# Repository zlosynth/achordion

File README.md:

# Achordion

Chord-crafting quantizing wavetable oscillator module for Eurorack.

* Wavetable synthesis, 37 wavetables, smooth transitions
* Up to 18 simultaneous voices
* Sub-octaves, duplicated tones, and chords
* 4 styles of playing - single tone, chords, arpeggios, intervals
* Quantization to selected scale
* Any scale can be played with the white piano keys
* Two lines with independent 1V/oct inputs and audio outputs
* LEDs visualizing dialed parameters
* Based around Electro-Smith's [Daisy Patch SM](https://www.electro-smith.com/daisy/patch-sm) platform
* Programmed in Rust

Find more details about the module, including a feature overview video and a
user manual, on its [website](https://zlosynth.com/achordion).

# Firmware

If you wish to upgrade to a newer version of firmware, refer to the respective
[Release description](https://github.com/zlosynth/achordion/releases).

# Development

See [DEVELOPMENT.md](DEVELOPMENT.md) to find some basic commands to interact
with the project. To learn more, read the code. A good place to start would be
[eurorack/src/main.rs](eurorack/src/main.rs).

# License

Software of Achordion is distributed under the terms of the General Public
License version 3. See [LICENSE-SOFTWARE](LICENSE-SOFTWARE) for details.

Schematics and PCB layout are distributed under the terms of Creative Commons
BY-SA. See [LICENSE-HARDWARE](LICENSE-HARDWARE) for details. Parts of the
schematics are based on [Emilie Gillet's Mutable
Instruments](https://github.com/pichenettes/eurorack), kudos to her for making
them open.

The manual is distributed under the terms of Creative Commons BY-SA too. See
[LICENSE-MANUAL](LICENSE-MANUAL) for details.

# Changelog

Read the [CHANGELOG.md](CHANGELOG.md) to learn about changes introduced in each
release.

# Versioning

See [VERSIONING.md](VERSIONING.md) to find detailed information about versioning
of the project and compatability between its software and hardware.

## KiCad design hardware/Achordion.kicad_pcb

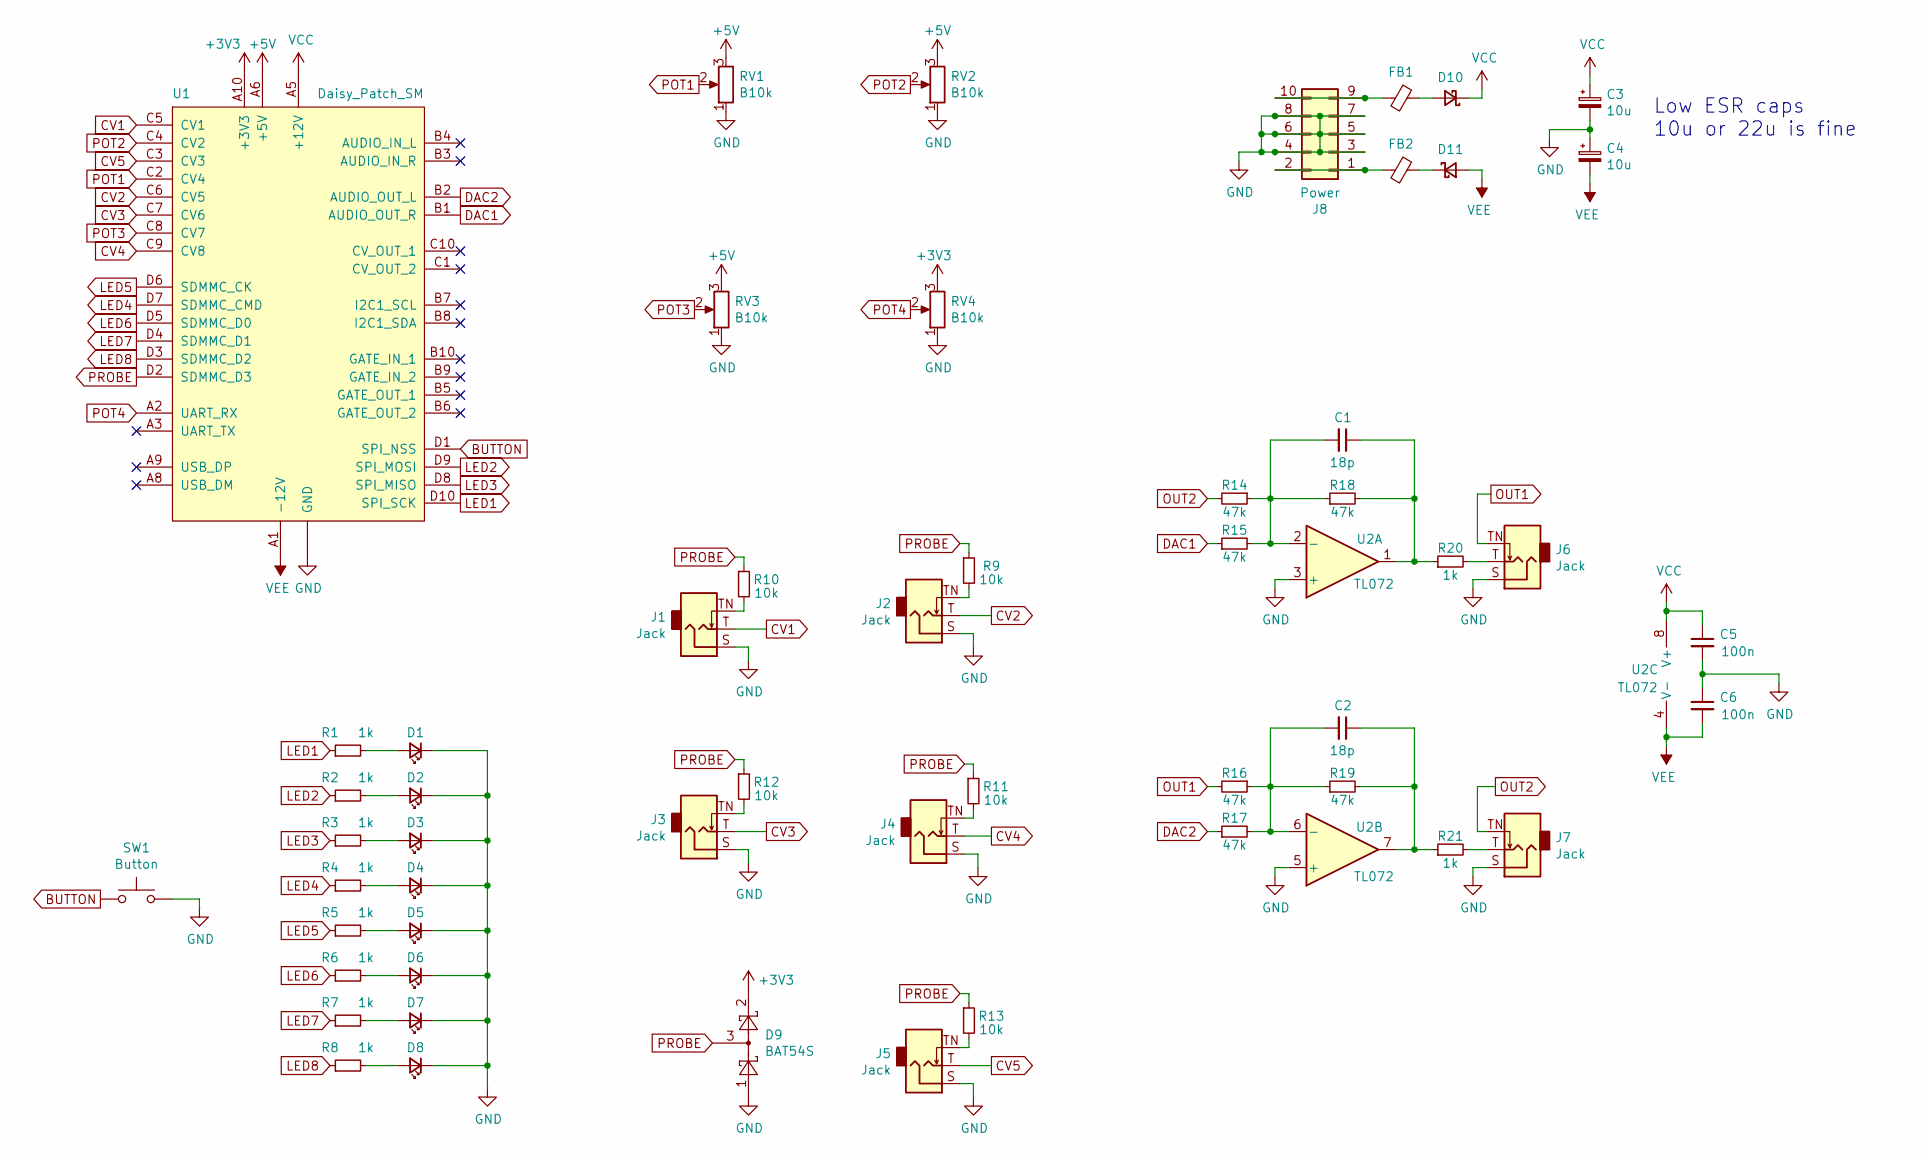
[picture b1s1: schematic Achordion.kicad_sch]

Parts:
C1, C2: 18p; C_0805_2012Metric_Pad1.18x1.45mm_HandSolder; Mfr Part Number CL10C180JB81PNC; LCSC C1647
C3, C4: 10u; CP_Elec_5x5.8; Mfr Part Number T491B226M016AT; LCSC C122226
C5, C6: 100n; C_0805_2012Metric_Pad1.18x1.45mm_HandSolder; Mfr Part Number CL10F104ZO8NNNC; LCSC C14663
D1, D2, D3, D4, D5, D6, D7, D8: LED; LED_D3.0mm; Mfr Part Number WP710A10SRD/D
D9: BAT54S; SOT-23_Handsoldering; Mfr Part Number BAT54S,215
D10, D11: Schottky; D_SOD-123; Mfr Part Number STPS0540ZY; LCSC C8598
FB1, FB2: FB; L_0805_2012Metric_Pad1.05x1.20mm_HandSolder
J1, J2, J3, J4, J5, J6, J7: Jack; Jack_3.5mm_QingPu_WQP-PJ398SM_Vertical_CircularHoles
J8: Power; Power_Connector_Connfly; Mfr Part Number 87914-1016
R1, R2, R3, R4, R5, R6, R7, R8: 1k; R_0805_2012Metric_Pad1.20x1.40mm_HandSolder; Mfr Part Number CR0603-FX-3650ELF; LCSC C23032
R9, R10, R11, R12, R13: 10k; R_0805_2012Metric_Pad1.20x1.40mm_HandSolder; Mfr Part Number CR0603-FX-1002ELF; LCSC C25744
R14, R16, R18, R19: 47k; R_0805_2012Metric_Pad1.20x1.40mm_HandSolder; Mfr Part Number CR0603-FX-4702ELF; LCSC C25819
R15, R17: 47k; R_0805_2012Metric_Pad1.20x1.40mm_HandSolder; Mfr Part Number CR0603-JW-682ELF; LCSC C23212
R20, R21: 1k; R_0805_2012Metric_Pad1.20x1.40mm_HandSolder; Mfr Part Number CR0603-FX-1001ELF; LCSC C21190
RV1, RV2, RV3, RV4: B10k; Potentiometer_Alpha; Mfr Part Number RK09L1140A66
SW1: Button; SW_PUSH_6mm; Mfr Part Number SKHHDTA010
U1: Daisy_Patch_SM
U2: TL072; SOIC-8_3.9x4.9mm_P1.27mm; Mfr Part Number TL072CD; LCSC C163525

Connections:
+3V3: D9.2, RV4.3, U1.A10 (+3V3)
+5V: RV1.3, RV2.3, RV3.3, U1.A6 (+5V)
BUTTON: SW1.1, U1.D1 (SPI_NSS)
CV1: J1.T, U1.C5 (CV1)
CV2: J2.T, U1.C6 (CV5)
CV3: J3.T, U1.C7 (CV6)
CV4: J4.T, U1.C9 (CV8)
CV5: J5.T, U1.C3 (CV3)
DAC1: R15.1, U1.B1 (AUDIO_OUT_R)
DAC2: R17.1, U1.B2 (AUDIO_OUT_L)
GND: C3.2, C4.1, C5.2, C6.1, D1.1 (K), D2.1 (K), D3.1 (K), D4.1 (K), D5.1 (K), D6.1 (K), D7.1 (K), D8.1 (K), D9.1, J1.S, J2.S, J3.S, J4.S, J5.S, J6.S, J7.S, J8.3, J8.4, J8.5, J8.6, J8.7, J8.8, RV1.1, RV2.1, RV3.1, RV4.1, SW1.2, U1.A4 (GND), U1.A7 (GND), U2.3 (+), U2.5 (+)
LED1: R1.1, U1.D10 (SPI_SCK)
LED2: R2.1, U1.D9 (SPI_MOSI)
LED3: R3.1, U1.D8 (SPI_MISO)
LED4: R4.1, U1.D7 (SDMMC_CMD)
LED5: R5.1, U1.D6 (SDMMC_CK)
LED6: R6.1, U1.D5 (SDMMC_D0)
LED7: R7.1, U1.D4 (SDMMC_D1)
LED8: R8.1, U1.D3 (SDMMC_D2)
unnamed: C1.1, R18.2, R20.1, U2.1
unnamed: C2.1, R19.2, R21.1, U2.7
unnamed: D1.2 (A), R1.2
unnamed: D2.2 (A), R2.2
unnamed: D3.2 (A), R3.2
unnamed: D4.2 (A), R4.2
unnamed: D5.2 (A), R5.2
unnamed: D6.2 (A), R6.2
unnamed: D7.2 (A), R7.2
unnamed: D8.2 (A), R8.2
unnamed: D10.2 (A), FB1.1
unnamed: D11.1 (K), FB2.1
unnamed: J1.TN, R10.2
unnamed: J2.TN, R9.2
unnamed: J3.TN, R12.2
unnamed: J4.TN, R11.2
unnamed: J5.TN, R13.2
unnamed: J6.T, R20.2
unnamed: J7.T, R21.2
unnamed: FB2.2, J8.1, J8.2
unnamed: FB1.2, J8.9, J8.10
unnamed: C1.2, R14.1, R15.2, R18.1, U2.2 (-)
unnamed: C2.2, R16.1, R17.2, R19.1, U2.6 (-)
OUT1: J6.TN, R16.2
OUT2: J7.TN, R14.2
POT1: RV1.2, U1.C2 (CV4)
POT2: RV2.2, U1.C4 (CV2)
POT3: RV3.2, U1.C8 (CV7)
POT4: RV4.2, U1.A2 (UART_RX)
PROBE: D9.3, R9.1, R10.1, R11.1, R12.1, R13.1, U1.D2 (SDMMC_D3)
VCC: C3.1, C5.1, D10.1 (K), U1.A5 (+12V), U2.8 (V+)
VEE: C4.2, C6.2, D11.2 (A), U1.A1 (-12V), U2.4 (V-)

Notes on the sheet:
Low ESR caps 10u or 22u is fine

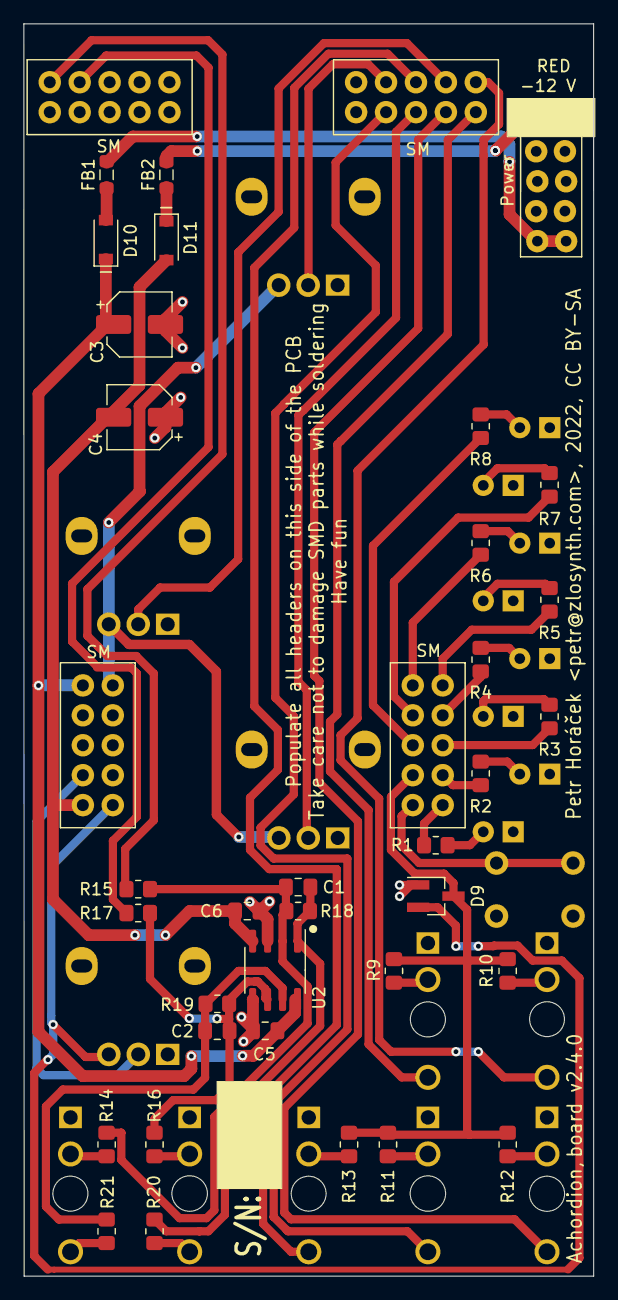
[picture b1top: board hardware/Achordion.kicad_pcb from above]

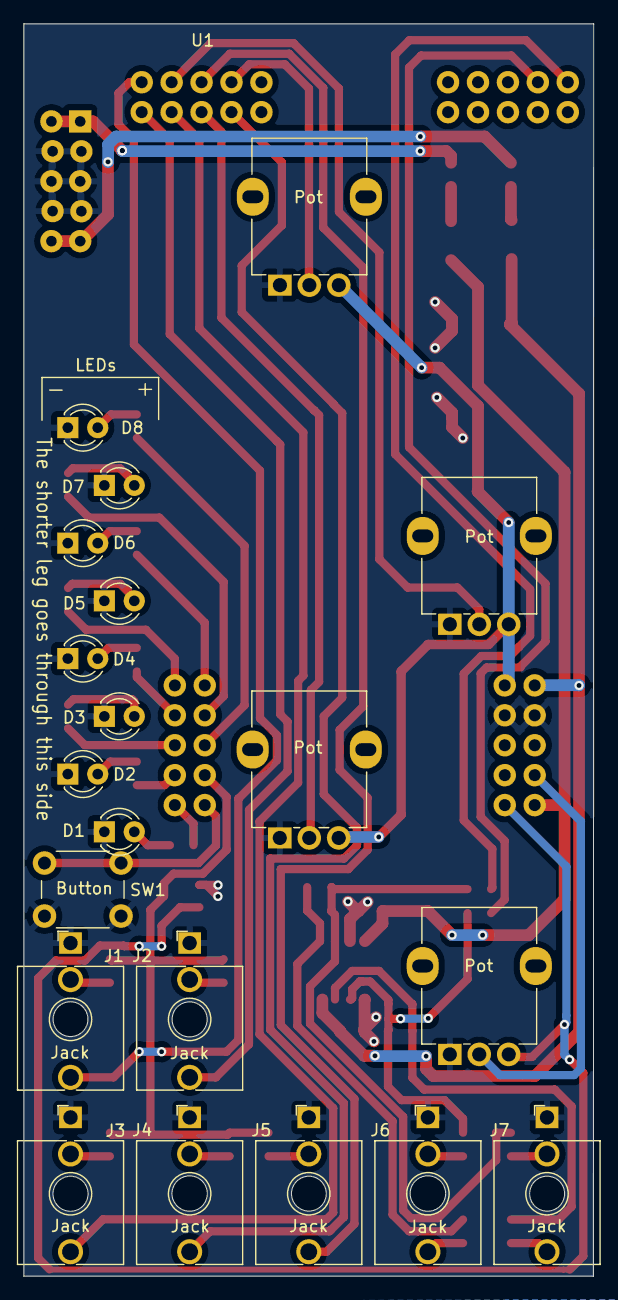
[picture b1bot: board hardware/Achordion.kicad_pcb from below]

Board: 2 copper layers, 48.4 x 106.3 mm, 55 parts (21 on the bottom side), 51 nets.

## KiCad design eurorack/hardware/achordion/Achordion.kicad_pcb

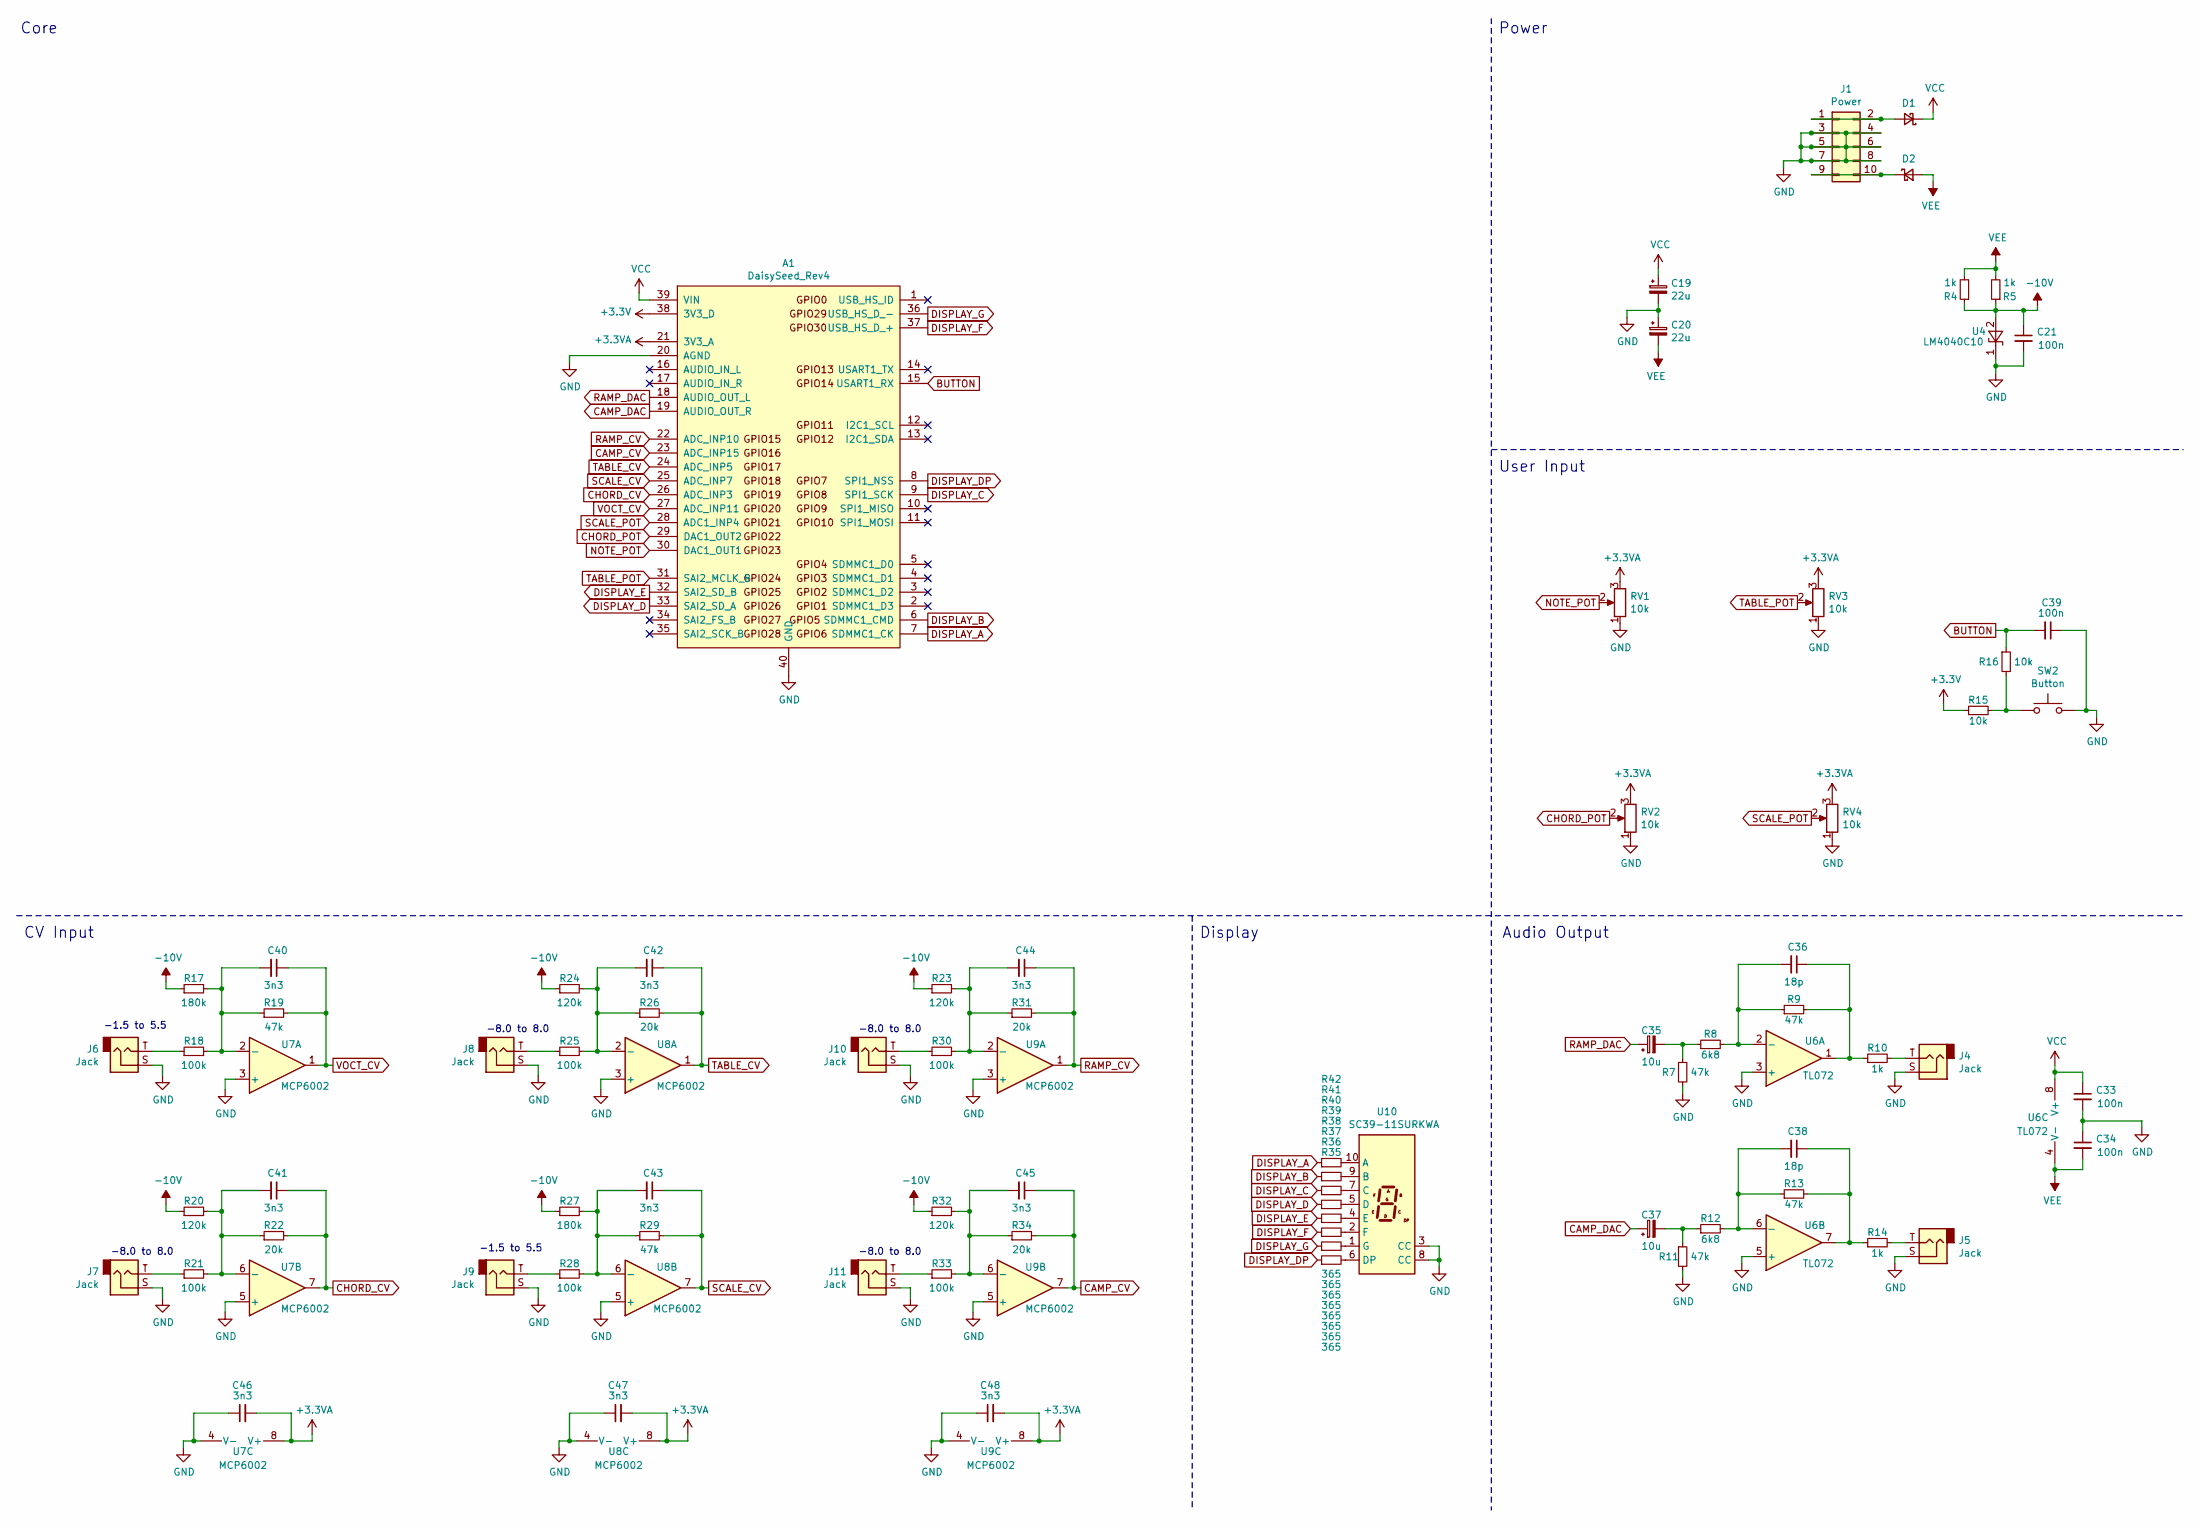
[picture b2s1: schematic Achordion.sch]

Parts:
A1: DaisySeed_Rev4; DaisySeed
C19, C20: 22u; CP_EIA-3528-21_Kemet-B; LCSC C122226
C21: 100n; C_1206_3216Metric; LCSC C24497
C33, C34, C39: 100n; C_0603_1608Metric; LCSC C14663
C35, C37: 10u; CP_EIA-3216-18_Kemet-A; LCSC C7171
C36, C38: 18p; C_0603_1608Metric; LCSC C1647
C40, C41, C42, C43, C44, C45, C46, C47, C48: 3n3; C_0603_1608Metric; LCSC C1613
D1, D2: D_Schottky_Small; D_SOD-123; LCSC C8598
J1: Power; PinHeader_2x05_P2.54mm_Vertical
J4, J5, J6, J7, J8, J9, J10, J11: Jack; Jack_3.5mm_QingPu_WQP-PJ398SM_Vertical_CircularHoles
R4, R5, R10, R14: 1k; R_0603_1608Metric; LCSC C21190
R7, R9, R11, R13, R19, R29: 47k; R_0603_1608Metric; LCSC C25819
R8, R12: 6k8; R_0603_1608Metric; LCSC C23212
R15, R16: 10k; R_0603_1608Metric; LCSC C25744
R17, R27: 180k; R_0603_1608Metric; LCSC C22827
R18, R21, R25, R28, R30, R33: 100k; R_0603_1608Metric; LCSC C25803
R20, R23, R24, R32: 120k; R_0603_1608Metric; LCSC C25808
R22, R26, R31, R34: 20k; R_0603_1608Metric; LCSC C4184
R35, R36, R37, R38, R39, R40, R41, R42: 365; R_0603_1608Metric; LCSC C23032
RV1, RV2, RV3, RV4: 10k; Potentiometer_Alps_RK09L_Single_Vertical
SW2: Button; SW_PUSH_6mm
U4: LM4040C10; SOT-23; LCSC C201738
U6: TL072; SOIC-8_3.9x4.9mm_P1.27mm; LCSC C163525
U7, U8, U9: MCP6002; SOIC-8_3.9x4.9mm_P1.27mm; LCSC C7377
U10: SC39-11SURKWA; Sx39-1xxxxx

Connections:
+3.3VA: A1.21 (3V3_A), C46.2, C47.2, C48.2, RV1.3, RV2.3, RV3.3, RV4.3, U7.8 (V+), U8.8 (V+), U9.8 (V+)
+3V3: A1.38 (3V3_D), R15.1
-10V: C21.1, R4.1, R5.1, R17.1, R20.1, R23.1, R24.1, R27.1, R32.1, U4.2 (A)
BUTTON: A1.15 (USART1_RX), C39.2, R16.1
CAMP_CV: A1.23 (ADC_INP15), C45.1, R34.2, U9.7
CAMP_DAC: A1.19 (AUDIO_OUT_R), C37.1
CHORD_CV: A1.26 (ADC_INP3), C41.1, R22.2, U7.7
CHORD_POT: A1.29 (DAC1_OUT2), RV2.2
DISPLAY_A: A1.7 (SDMMC1_CK), R35.1
DISPLAY_B: A1.6 (SDMMC1_CMD), R36.1
DISPLAY_C: A1.9 (SPI1_SCK), R37.1
DISPLAY_D: A1.33 (SAI2_SD_A), R38.1
DISPLAY_DP: A1.8 (SPI1_NSS), R42.1
DISPLAY_E: A1.32 (SAI2_SD_B), R39.1
DISPLAY_F: A1.37 (USB_HS_D_+), R40.1
DISPLAY_G: A1.36 (USB_HS_D_-), R41.1
GND: A1.20 (AGND), A1.40 (GND), C19.2, C20.1, C21.2, C33.2, C34.1, C39.1, C46.1, C47.1, C48.1, J1.3, J1.4, J1.5, J1.6, J1.7, J1.8, J4.S, J5.S, J6.S, J7.S, J8.S, J9.S, J10.S, J11.S, R7.2, R11.2, RV1.1, RV2.1, RV3.1, RV4.1, SW2.2, U4.1 (K), U6.3 (+), U6.5 (+), U7.3 (+), U7.4 (V-), U7.5 (+), U8.3 (+), U8.4 (V-), U8.5 (+), U9.3 (+), U9.4 (V-), U9.5 (+), U10.3 (CC), U10.8 (CC)
NOTE_POT: A1.30 (DAC1_OUT1), RV1.2
unnamed: C35.2, R7.1, R8.1
unnamed: C36.1, R9.2, R10.1, U6.1
unnamed: C36.2, R8.2, R9.1, U6.2 (-)
unnamed: C37.2, R11.1, R12.1
unnamed: C38.1, R13.2, R14.1, U6.7
unnamed: C38.2, R12.2, R13.1, U6.6 (-)
unnamed: C40.2, R17.2, R18.2, R19.1, U7.2 (-)
unnamed: C41.2, R20.2, R21.2, R22.1, U7.6 (-)
unnamed: C42.2, R24.2, R25.2, R26.1, U8.2 (-)
unnamed: C43.2, R27.2, R28.2, R29.1, U8.6 (-)
unnamed: C44.2, R23.2, R30.2, R31.1, U9.2 (-)
unnamed: C45.2, R32.2, R33.2, R34.1, U9.6 (-)
unnamed: D1.2 (A), J1.1, J1.2
unnamed: D2.1 (K), J1.9, J1.10
unnamed: J4.T, R10.2
unnamed: J5.T, R14.2
unnamed: J6.T, R18.1
unnamed: J7.T, R21.1
unnamed: J8.T, R25.1
unnamed: J9.T, R28.1
unnamed: J10.T, R30.1
unnamed: J11.T, R33.1
unnamed: R15.2, R16.2, SW2.1
unnamed: R35.2, U10.10 (A)
unnamed: R36.2, U10.9 (B)
unnamed: R37.2, U10.7 (C)
unnamed: R38.2, U10.5 (D)
unnamed: R39.2, U10.4 (E)
unnamed: R40.2, U10.2 (F)
unnamed: R41.2, U10.1 (G)
unnamed: R42.2, U10.6 (DP)
RAMP_CV: A1.22 (ADC_INP10), C44.1, R31.2, U9.1
RAMP_DAC: A1.18 (AUDIO_OUT_L), C35.1
SCALE_CV: A1.25 (ADC_INP7), C43.1, R29.2, U8.7
SCALE_POT: A1.28 (ADC1_INP4), RV4.2
TABLE_CV: A1.24 (ADC_INP5), C42.1, R26.2, U8.1
TABLE_POT: A1.31 (SAI2_MCLK_B), RV3.2
VCC: A1.39 (VIN), C19.1, C33.1, D1.1 (K), U6.8 (V+)
VEE: C20.2, C34.2, D2.2 (A), R4.2, R5.2, U6.4 (V-)
VOCT_CV: A1.27 (ADC_INP11), C40.1, R19.2, U7.1

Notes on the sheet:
Audio Output
Power
Display
CV Input
-1.5 to 5.5
-8.0 to 8.0
User Input
Core

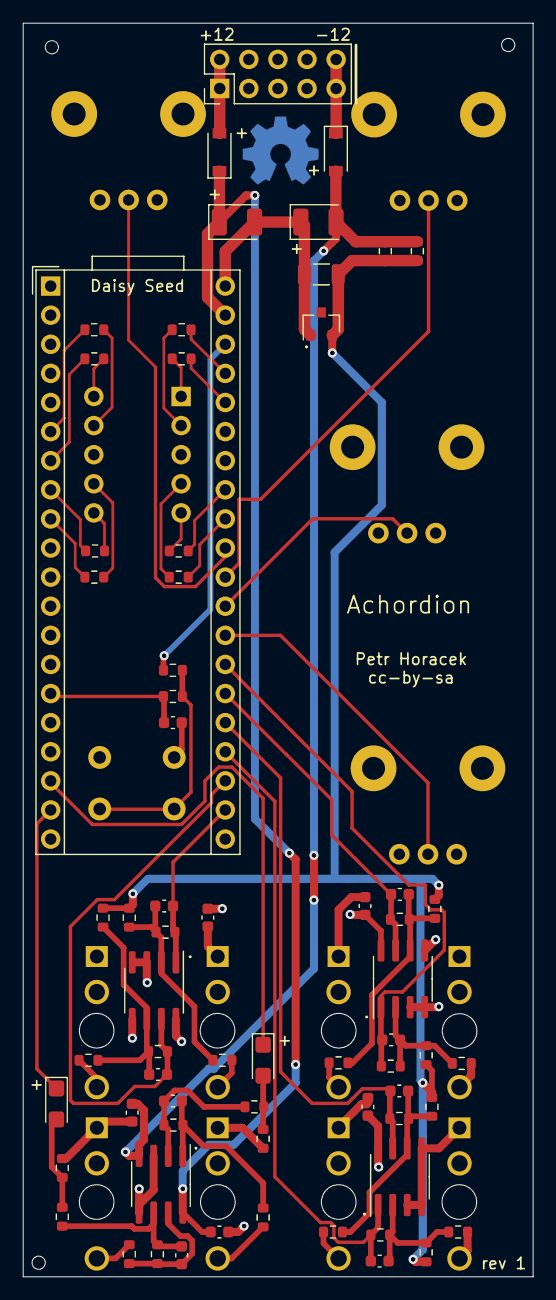
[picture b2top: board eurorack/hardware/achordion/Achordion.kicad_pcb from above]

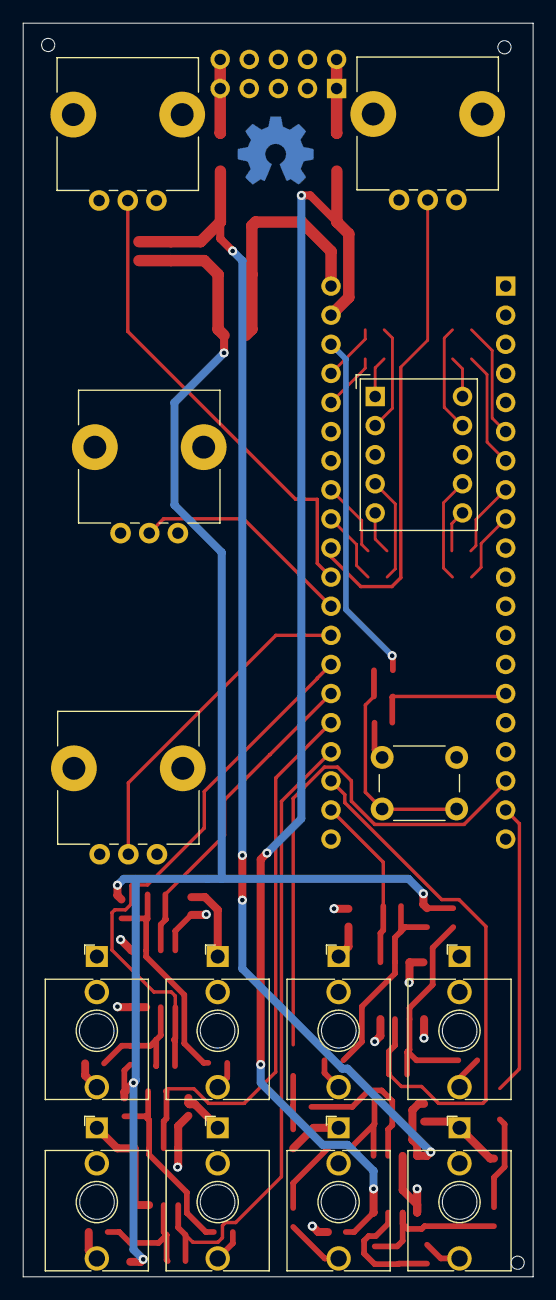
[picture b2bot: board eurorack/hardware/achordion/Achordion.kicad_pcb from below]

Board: 4 copper layers, 44.5 x 109.4 mm, 80 parts (14 on the bottom side), 58 nets.

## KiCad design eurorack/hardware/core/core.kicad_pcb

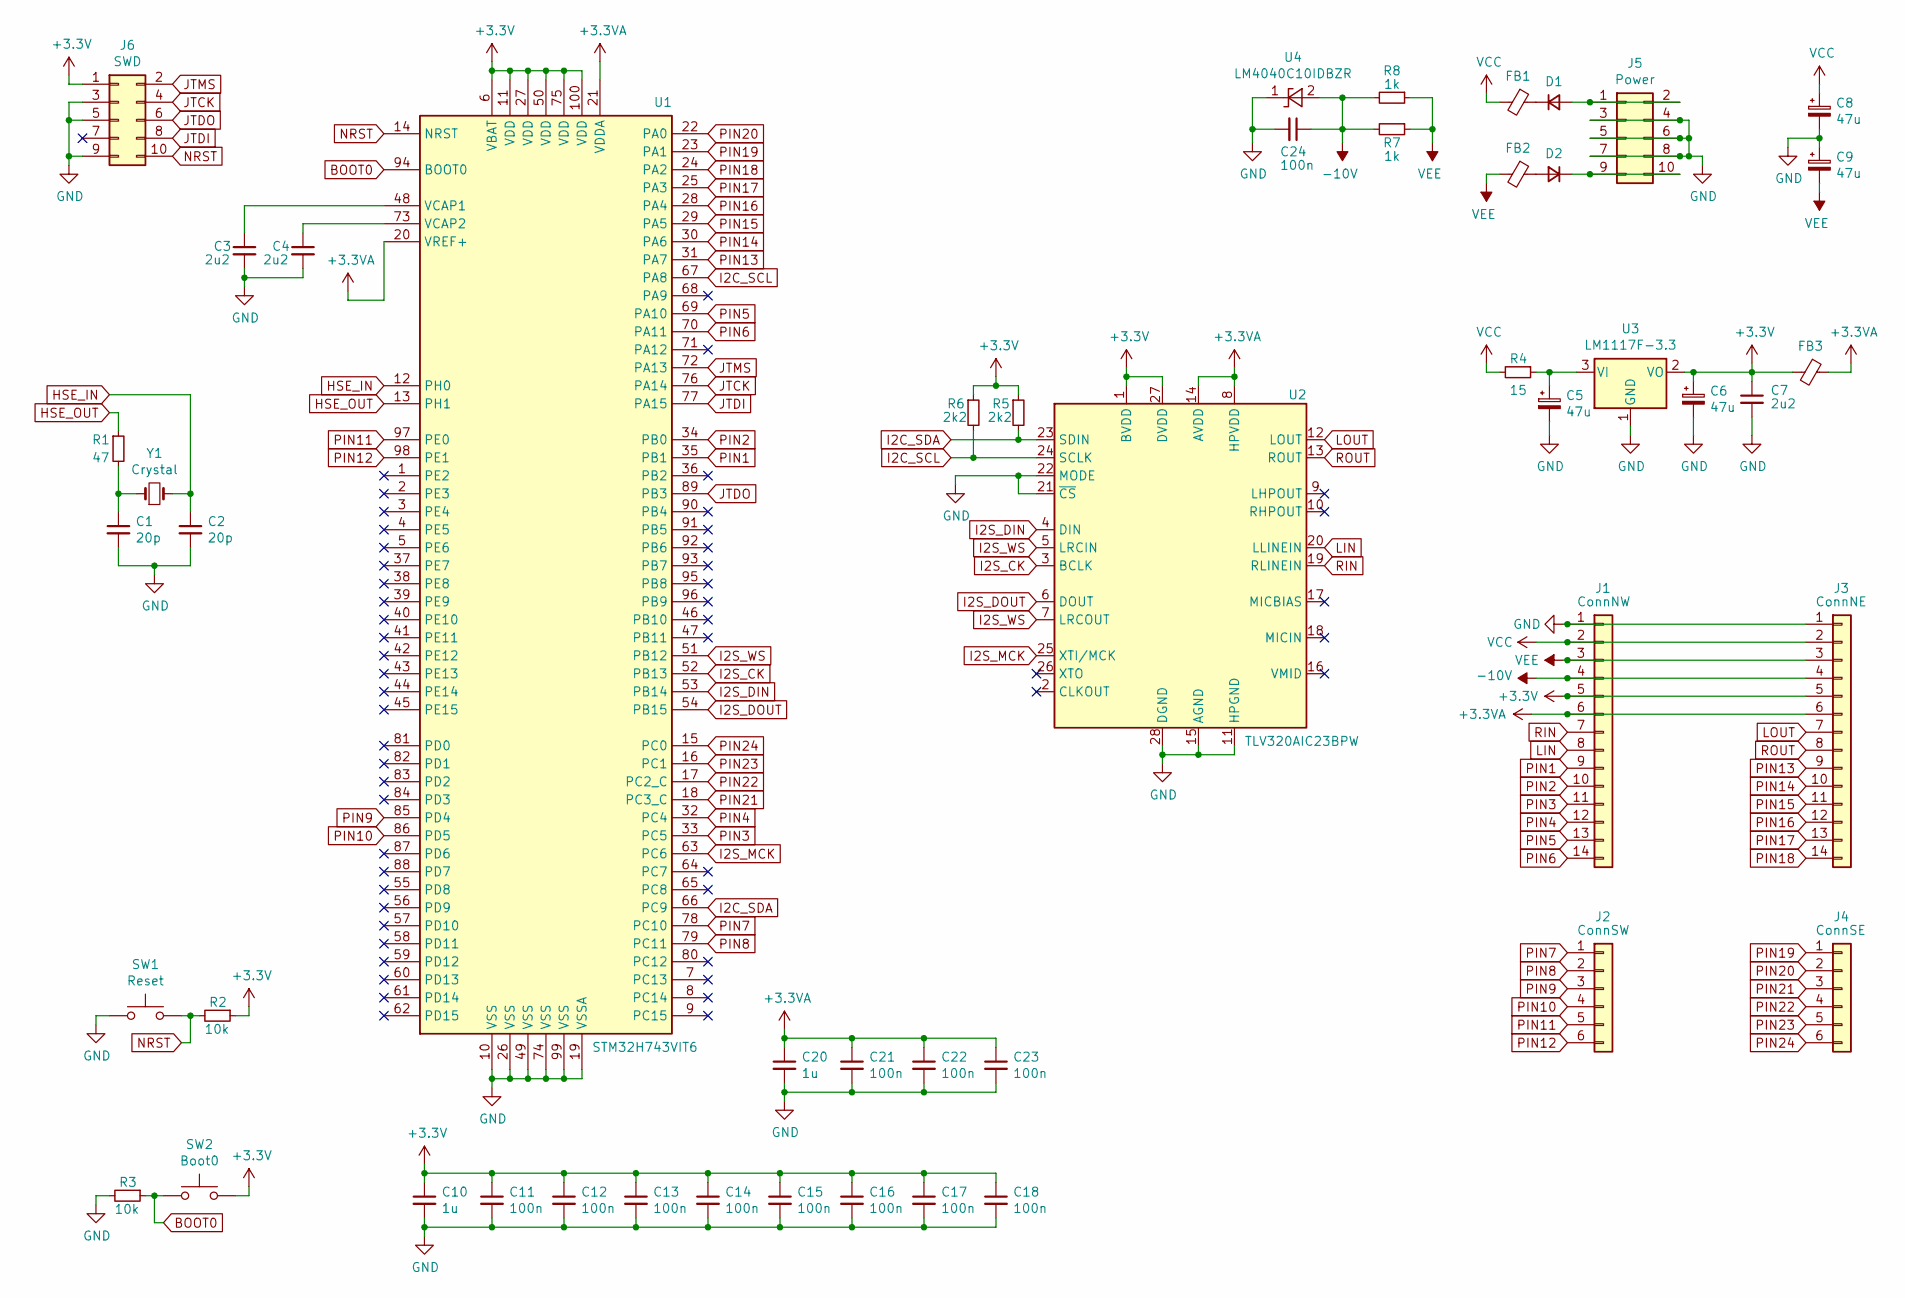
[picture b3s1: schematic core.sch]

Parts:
C1, C2: 20p; C_0402_1005Metric; LCSC Part # C1554
C3, C4, C7: 2u2; C_0603_1608Metric; LCSC Part # C23630
C5, C6, C8, C9: 47u; CP_EIA-3216-18_Kemet-A; LCSC Part # C129570
C10, C20: 1u; C_0402_1005Metric; LCSC Part # C52923
C11, C12, C13, C14, C15, C16, C17, C18, C21, C22, C23: 100n; C_0402_1005Metric; LCSC Part # C1525
C24: 100n; C_0805_2012Metric; LCSC Part # C49678
D1, D2: D_Small; D_SOD-123; LCSC Part # C8598
FB1, FB2, FB3: Ferrite_Bead_Small; L_0805_2012Metric; LCSC Part # C1017
J1: ConnNW; PinHeader_1x14_P2.54mm_Vertical
J2: ConnSW; PinHeader_1x06_P2.54mm_Vertical
J3: ConnNE; PinHeader_1x14_P2.54mm_Vertical
J4: ConnSE; PinHeader_1x06_P2.54mm_Vertical
J5: Power; PinHeader_2x05_P2.54mm_Vertical
J6: SWD; PinHeader_2x05_P1.27mm_Vertical
R1: 47; R_0402_1005Metric; LCSC Part # C25118
R2, R3: 10k; R_0402_1005Metric; LCSC Part # C25744
R4: 15; R_0603_1608Metric; LCSC Part # C22810
R5, R6: 2k2; R_0402_1005Metric; LCSC Part # C25879
R7, R8: 1k; R_0805_2012Metric; LCSC Part # C17513
SW1: Reset; SW_Push_SPST_NO_Alps_SKRK; LCSC Part # C115357
SW2: Boot0; SW_Push_SPST_NO_Alps_SKRK; LCSC Part # C115357
U1: STM32H743VIT6; LQFP-100_14x14mm_P0.5mm; LCSC C114409
U2: TLV320AIC23BPW; TSSOP-28_4.4x9.7mm_P0.65mm; LCSC Part # C9915
U3: LM1117F-3.3; SOT-89-3; LCSC Part # C126019
U4: LM4040C10IDBZR; SOT-23; LCSC Part # C201738
Y1: Crystal; Crystal_SMD_5032-2Pin_5.0x3.2mm; LCSC Part # C115962

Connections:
+3.3VA: C20.1, C21.1, C22.1, C23.1, FB3.1, J1.6, J3.6, U1.20 (VREF+), U1.21 (VDDA), U2.8 (HPVDD), U2.14 (AVDD)
+3V3: C6.1, C7.1, C10.1, C11.1, C12.1, C13.1, C14.1, C15.1, C16.1, C17.1, C18.1, FB3.2, J1.5, J3.5, J6.1, R2.1, R5.1, R6.1, SW2.2, U1.6 (VBAT), U1.11 (VDD), U1.27 (VDD), U1.50 (VDD), U1.75 (VDD), U1.100 (VDD), U2.1 (BVDD), U2.27 (DVDD), U3.2 (VO)
-10V: C24.1, J1.4, J3.4, R7.2, R8.2, U4.2 (A)
BOOT0: R3.1, SW2.1, U1.94 (BOOT0)
GND: C1.2, C2.2, C3.2, C4.2, C5.2, C6.2, C7.2, C8.2, C9.1, C10.2, C11.2, C12.2, C13.2, C14.2, C15.2, C16.2, C17.2, C18.2, C20.2, C21.2, C22.2, C23.2, C24.2, J1.1, J3.1, J5.3, J5.4, J5.5, J5.6, J5.7, J5.8, J6.3, J6.5, J6.9, R3.2, SW1.1, U1.10 (VSS), U1.19 (VSSA), U1.26 (VSS), U1.49 (VSS), U1.74 (VSS), U1.99 (VSS), U2.11 (HPGND), U2.15 (AGND), U2.21 (~CS~), U2.22 (MODE), U2.28 (DGND), U3.1 (GND), U4.1 (K)
HSE_IN: C2.1, U1.12 (PH0), Y1.2
HSE_OUT: R1.1, U1.13 (PH1)
I2C_SCL: R6.2, U1.67 (PA8), U2.24 (SCLK)
I2C_SDA: R5.2, U1.66 (PC9), U2.23 (SDIN)
I2S_CK: U1.52 (PB13), U2.3 (BCLK)
I2S_DIN: U1.53 (PB14), U2.4 (DIN)
I2S_DOUT: U1.54 (PB15), U2.6 (DOUT)
I2S_MCK: U1.63 (PC6), U2.25 (XTI/MCK)
I2S_WS: U1.51 (PB12), U2.5 (LRCIN), U2.7 (LRCOUT)
JTCK: J6.4, U1.76 (PA14)
JTDI: J6.8, U1.77 (PA15)
JTDO: J6.6, U1.89 (PB3)
JTMS: J6.2, U1.72 (PA13)
LIN: J1.8, U2.20 (LLINEIN)
LOUT: J3.7, U2.12 (LOUT)
NRST: J6.10, R2.2, SW1.2, U1.14 (NRST)
unnamed: C1.1, R1.2, Y1.1
unnamed: C3.1, U1.48 (VCAP1)
unnamed: C4.1, U1.73 (VCAP2)
unnamed: C5.1, R4.1, U3.3 (VI)
unnamed: D1.1 (K), FB1.1
unnamed: D1.2 (A), J5.1, J5.2
unnamed: D2.1 (K), J5.9, J5.10
unnamed: D2.2 (A), FB2.1
PIN1: J1.9, U1.35 (PB1)
PIN2: J1.10, U1.34 (PB0)
PIN3: J1.11, U1.33 (PC5)
PIN4: J1.12, U1.32 (PC4)
PIN5: J1.13, U1.69 (PA10)
PIN6: J1.14, U1.70 (PA11)
PIN7: J2.1, U1.78 (PC10)
PIN8: J2.2, U1.79 (PC11)
PIN9: J2.3, U1.85 (PD4)
PIN10: J2.4, U1.86 (PD5)
PIN11: J2.5, U1.97 (PE0)
PIN12: J2.6, U1.98 (PE1)
PIN13: J3.9, U1.31 (PA7)
PIN14: J3.10, U1.30 (PA6)
PIN15: J3.11, U1.29 (PA5)
PIN16: J3.12, U1.28 (PA4)
PIN17: J3.13, U1.25 (PA3)
PIN18: J3.14, U1.24 (PA2)
PIN19: J4.1, U1.23 (PA1)
PIN20: J4.2, U1.22 (PA0)
PIN21: J4.3, U1.18 (PC3_C)
PIN22: J4.4, U1.17 (PC2_C)
PIN23: J4.5, U1.16 (PC1)
PIN24: J4.6, U1.15 (PC0)
RIN: J1.7, U2.19 (RLINEIN)
ROUT: J3.8, U2.13 (ROUT)
VCC: C8.1, FB1.2, J1.2, J3.2, R4.2
VEE: C9.2, FB2.2, J1.3, J3.3, R7.1, R8.1

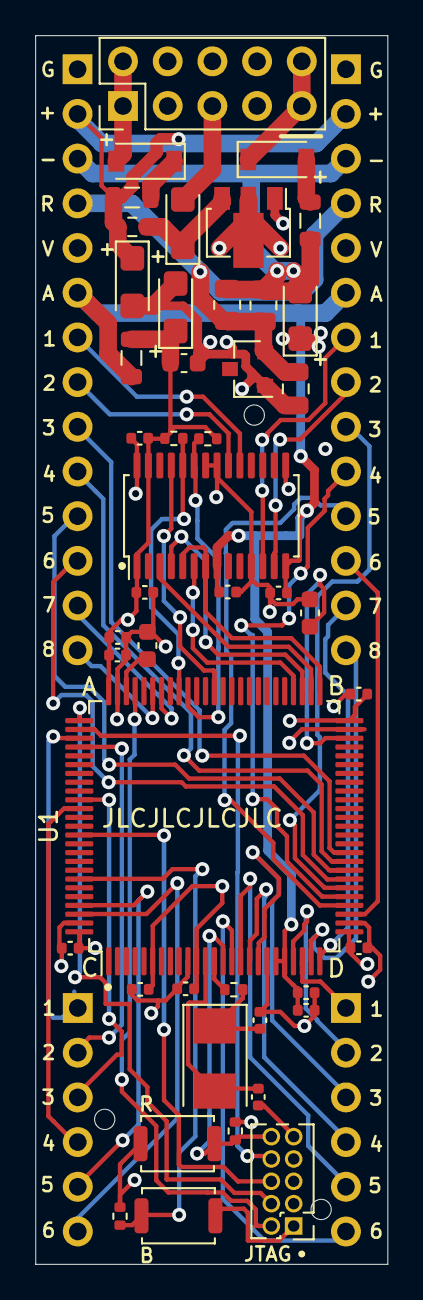
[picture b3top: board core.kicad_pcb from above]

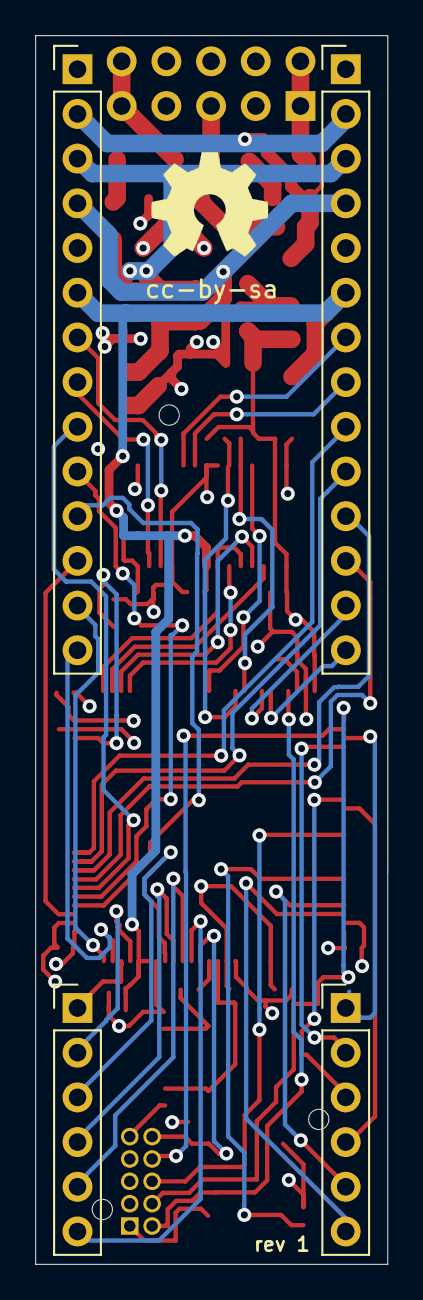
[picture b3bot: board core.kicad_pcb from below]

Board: 4 copper layers, 20.0 x 69.8 mm, 49 parts (4 on the bottom side), 57 nets.

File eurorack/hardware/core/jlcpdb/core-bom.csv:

Comment,Designator,Footprint,LCSC
"20p","C1,C2","Capacitor_SMD:C_0402_1005Metric","C1554"
"1u","C10,C20","Capacitor_SMD:C_0402_1005Metric","C52923"
"100n","C11,C12,C13,C14,C15,C16,C17,C18,C19,C21,C22,C23","Capacitor_SMD:C_0402_1005Metric","C1525"
"100n","C24","Capacitor_SMD:C_0805_2012Metric","C49678"
"2u2","C3,C4,C7","Capacitor_SMD:C_0603_1608Metric","C23630"
"47u","C5,C6,C8,C9","Capacitor_Tantalum_SMD:CP_EIA-3216-18_Kemet-A","C129570"
"D_Small","D1,D2","Diode_SMD:D_SOD-123","C8598"
"Ferrite_Bead_Small","FB1,FB2,FB3","Inductor_SMD:L_0805_2012Metric","C1017"
"ConnNW","J1","Connector_PinHeader_2.54mm:PinHeader_1x14_P2.54mm_Vertical",""
"ConnSW","J2","Connector_PinHeader_2.54mm:PinHeader_1x06_P2.54mm_Vertical",""
"ConnNE","J3","Connector_PinHeader_2.54mm:PinHeader_1x14_P2.54mm_Vertical",""
"ConnSE","J4","Connector_PinHeader_2.54mm:PinHeader_1x06_P2.54mm_Vertical",""
"Power","J5","Connector_PinHeader_2.54mm:PinHeader_2x05_P2.54mm_Vertical",""
"SWD","J6","Connector_PinHeader_1.27mm:PinHeader_2x05_P1.27mm_Vertical",""
"47","R1","Resistor_SMD:R_0402_1005Metric","C25118"
"10k","R2,R3","Resistor_SMD:R_0402_1005Metric","C25744"
"15","R4","Resistor_SMD:R_0603_1608Metric","C22810"
"2k2","R5,R6","Resistor_SMD:R_0402_1005Metric","C25879"
"1k","R7,R8","Resistor_SMD:R_0805_2012Metric","C17513"
"Reset","SW1","Button_Switch_SMD:SW_Push_SPST_NO_Alps_SKRK","C115357"
"Boot0","SW2","Button_Switch_SMD:SW_Push_SPST_NO_Alps_SKRK","C115357"
" STM32F427VGT6","U1","Package_QFP:LQFP-100_14x14mm_P0.5mm","C117815"
"TLV320AIC23BPW","U2","Package_SO:TSSOP-28_4.4x9.7mm_P0.65mm","C9915"
" LM1117F-3.3","U3","Package_TO_SOT_SMD:SOT-89-3","C126019"
"LM4040C10IDBZR","U4","Package_TO_SOT_SMD:SOT-23","C201738"
"Crystal","Y1","Crystal:Crystal_SMD_5032-2Pin_5.0x3.2mm","C115962"

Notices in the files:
eurorack/hardware/Achordion.sch:
cc-by-sa
hardware/Achordion.kicad_pcb:
Petr Horáček , 2022, CC BY-SA
